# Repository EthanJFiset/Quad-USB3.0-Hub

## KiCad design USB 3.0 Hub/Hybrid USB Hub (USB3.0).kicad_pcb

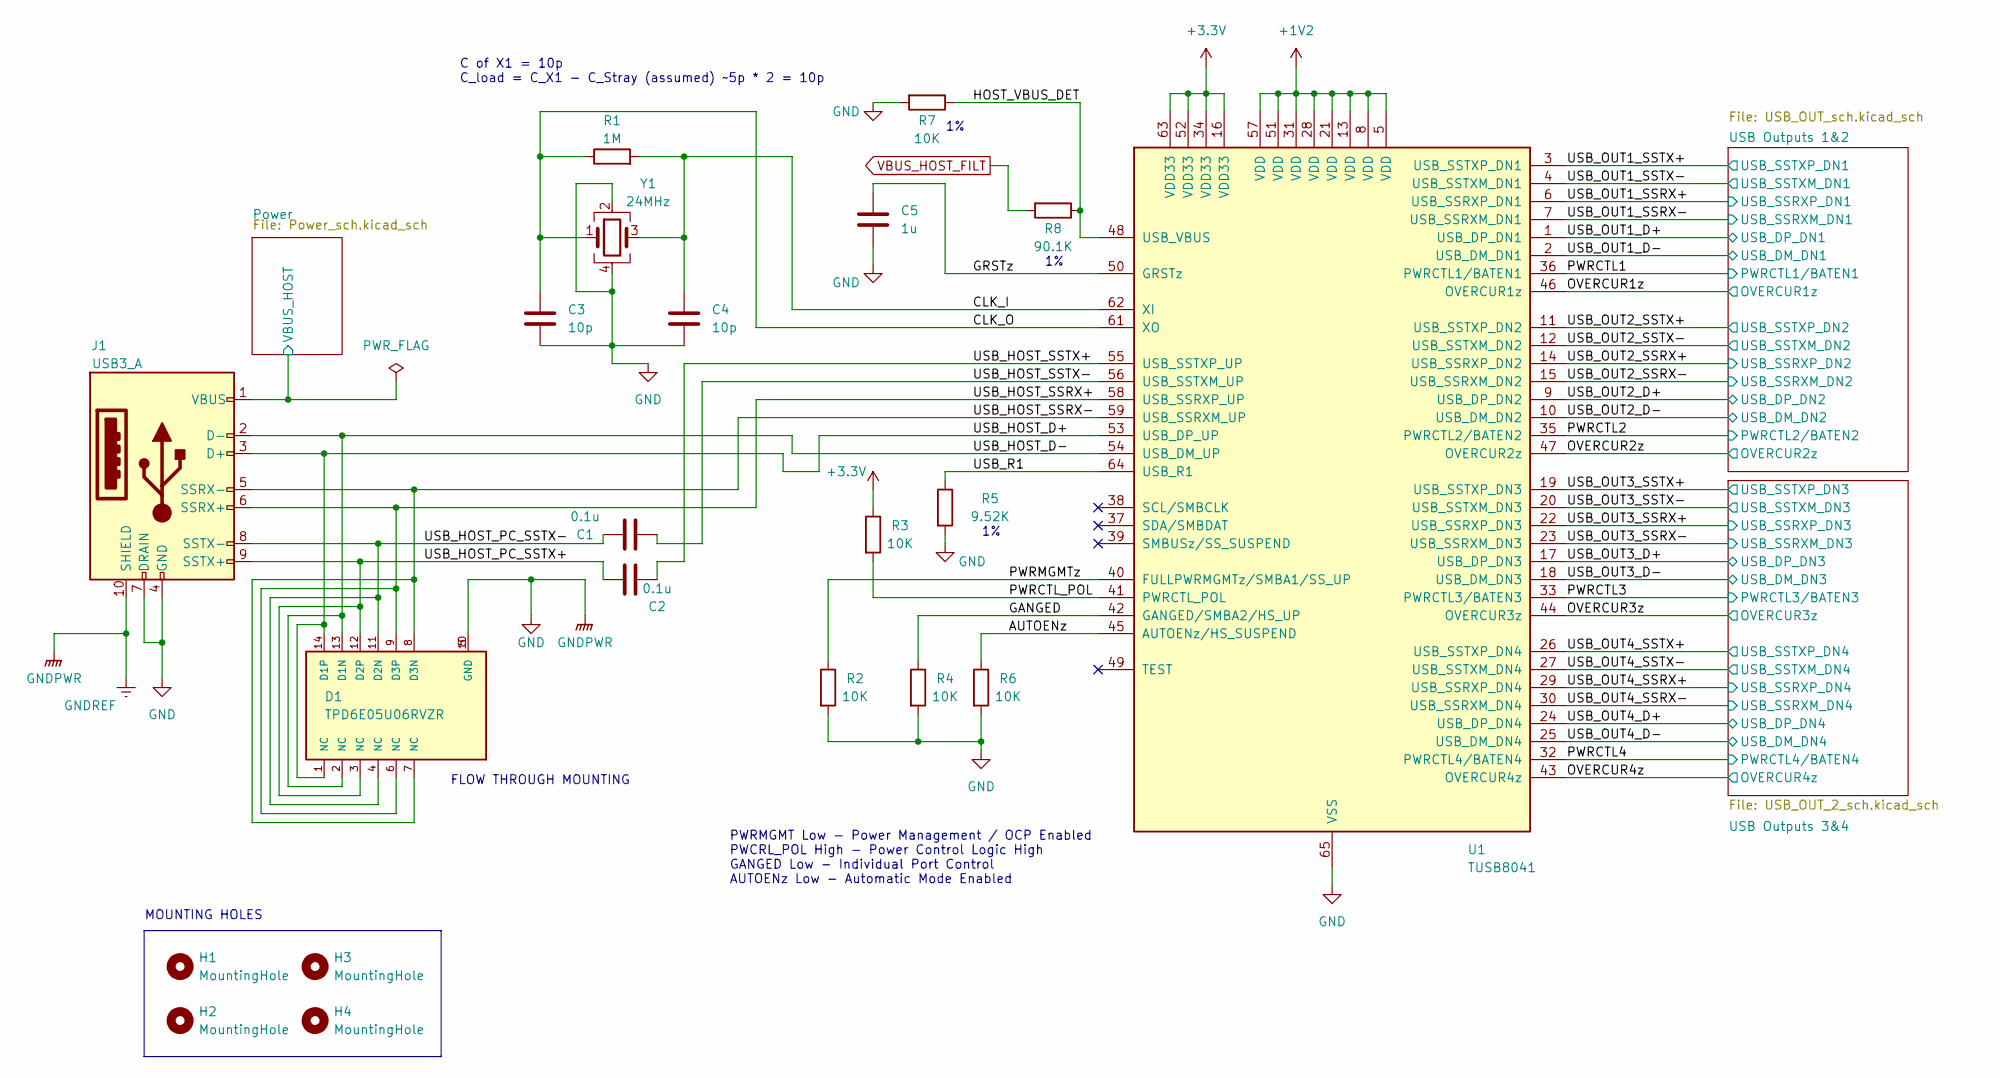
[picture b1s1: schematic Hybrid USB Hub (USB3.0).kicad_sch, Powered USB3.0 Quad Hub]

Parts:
C1, C2: 0.1u; C_0402_1005Metric
C3, C4: 10p; C_0402_1005Metric
C5: 1u; C_0402_1005Metric
D1: TPD6E05U06RVZR; PARTREV L
H1, H2, H3, H4: MountingHole; MountingHole_3.2mm_M3
J1: USB3_A; USB3_A_Molex_48393-001
R1: 1M; R_0402_1005Metric
R2, R3, R4, R6, R7: 10K; R_0402_1005Metric
R5: 9.52K; R_0402_1005Metric
R8: 90.1K; R_0402_1005Metric
U1: TUSB8041; QFN-64-1EP_9x9mm_P0.5mm_EP6x6mm_ThermalVias
Y1: 24MHz; Crystal_SMD_3225-4Pin_3.2x2.5mm

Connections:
+1V2: U1.5 (VDD), U1.8 (VDD), U1.13 (VDD), U1.21 (VDD), U1.28 (VDD), U1.31 (VDD), U1.51 (VDD), U1.57 (VDD); also elsewhere on the board
+3.3V: R3.1, U1.16 (VDD33), U1.34 (VDD33), U1.52 (VDD33), U1.63 (VDD33); also elsewhere on the board
/AUTOENz: R6.1, U1.45 (AUTOENz/HS_SUSPEND)
/CLK_I: C4.1, R1.2, U1.62 (XI), Y1.3
/CLK_O: C3.1, R1.1, U1.61 (XO), Y1.1
/GANGED: R4.1, U1.42 (GANGED/SMBA2/HS_UP)
/GRSTz: C5.1, U1.50 (GRSTz)
/HOST_VBUS_DET: R7.1, R8.1, U1.48 (USB_VBUS)
/OVERCUR1z: U1.46 (OVERCUR1z); also elsewhere on the board
/OVERCUR2z: U1.47 (OVERCUR2z); also elsewhere on the board
/OVERCUR3z: U1.44 (OVERCUR3z); also elsewhere on the board
/OVERCUR4z: U1.43 (OVERCUR4z); also elsewhere on the board
/PWRCTL1: U1.36 (PWRCTL1/BATEN1); also elsewhere on the board
/PWRCTL2: U1.35 (PWRCTL2/BATEN2); also elsewhere on the board
/PWRCTL3: U1.33 (PWRCTL3/BATEN3); also elsewhere on the board
/PWRCTL4: U1.32 (PWRCTL4/BATEN4); also elsewhere on the board
/PWRCTL_POL: R3.2, U1.41 (PWRCTL_POL)
/PWRMGMTz: R2.1, U1.40 (FULLPWRMGMTz/SMBA1/SS_UP)
/Power/VBUS_HOST: J1.1 (VBUS); also elsewhere on the board
/USB_HOST_D+: D1.1 (NC), D1.14 (D1P), J1.3 (D+), U1.53 (USB_DP_UP)
/USB_HOST_D-: D1.2 (NC), D1.13 (D1N), J1.2 (D-), U1.54 (USB_DM_UP)
/USB_HOST_PC_SSTX+: C2.2, D1.3 (NC), D1.12 (D2P), J1.9 (SSTX+)
/USB_HOST_PC_SSTX-: C1.2, D1.4 (NC), D1.11 (D2N), J1.8 (SSTX-)
/USB_HOST_SSRX+: D1.6 (NC), D1.9 (D3P), J1.6 (SSRX+), U1.58 (USB_SSRXP_UP)
/USB_HOST_SSRX-: D1.7 (NC), D1.8 (D3N), J1.5 (SSRX-), U1.59 (USB_SSRXM_UP)
/USB_HOST_SSTX+: C2.1, U1.55 (USB_SSTXP_UP)
/USB_HOST_SSTX-: C1.1, U1.56 (USB_SSTXM_UP)
/USB_OUT1_D+: U1.1 (USB_DP_DN1); also elsewhere on the board
/USB_OUT1_D-: U1.2 (USB_DM_DN1); also elsewhere on the board
/USB_OUT1_SSRX+: U1.6 (USB_SSRXP_DN1); also elsewhere on the board
/USB_OUT1_SSRX-: U1.7 (USB_SSRXM_DN1); also elsewhere on the board
/USB_OUT1_SSTX+: U1.3 (USB_SSTXP_DN1); also elsewhere on the board
/USB_OUT1_SSTX-: U1.4 (USB_SSTXM_DN1); also elsewhere on the board
/USB_OUT2_D+: U1.9 (USB_DP_DN2); also elsewhere on the board
/USB_OUT2_D-: U1.10 (USB_DM_DN2); also elsewhere on the board
/USB_OUT2_SSRX+: U1.14 (USB_SSRXP_DN2); also elsewhere on the board
/USB_OUT2_SSRX-: U1.15 (USB_SSRXM_DN2); also elsewhere on the board
/USB_OUT2_SSTX+: U1.11 (USB_SSTXP_DN2); also elsewhere on the board
/USB_OUT2_SSTX-: U1.12 (USB_SSTXM_DN2); also elsewhere on the board
/USB_OUT3_D+: U1.17 (USB_DP_DN3); also elsewhere on the board
/USB_OUT3_D-: U1.18 (USB_DM_DN3); also elsewhere on the board
/USB_OUT3_SSRX+: U1.22 (USB_SSRXP_DN3); also elsewhere on the board
/USB_OUT3_SSRX-: U1.23 (USB_SSRXM_DN3); also elsewhere on the board
/USB_OUT3_SSTX+: U1.19 (USB_SSTXP_DN3); also elsewhere on the board
/USB_OUT3_SSTX-: U1.20 (USB_SSTXM_DN3); also elsewhere on the board
/USB_OUT4_D+: U1.24 (USB_DP_DN4); also elsewhere on the board
/USB_OUT4_D-: U1.25 (USB_DM_DN4); also elsewhere on the board
/USB_OUT4_SSRX+: U1.29 (USB_SSRXP_DN4); also elsewhere on the board
/USB_OUT4_SSRX-: U1.30 (USB_SSRXM_DN4); also elsewhere on the board
/USB_OUT4_SSTX+: U1.26 (USB_SSTXP_DN4); also elsewhere on the board
/USB_OUT4_SSTX-: U1.27 (USB_SSTXM_DN4); also elsewhere on the board
/USB_R1: R5.1, U1.64 (USB_R1)
GND: C3.2, C4.2, C5.2, D1.5 (GND), D1.10 (GND), J1.4 (GND), J1.7 (DRAIN), J1.10 (SHIELD), R2.2, R4.2, R5.2, R6.2, R7.2, U1.65 (VSS), Y1.2, Y1.4; also elsewhere on the board
VBUS_HOST_FILT: R8.2

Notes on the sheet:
MOUNTING HOLES
FLOW THROUGH MOUNTING
C of X1 = 10p C_load = C_X1 - C_Stray (assumed) ~5p * 2 = 10p
PWRMGMT Low - Power Management / OCP Enabled PWCRL_POL High - Power Control Logic High GANGED Low - Individual Port Control AUTOENz Low - Automatic Mode Enabled

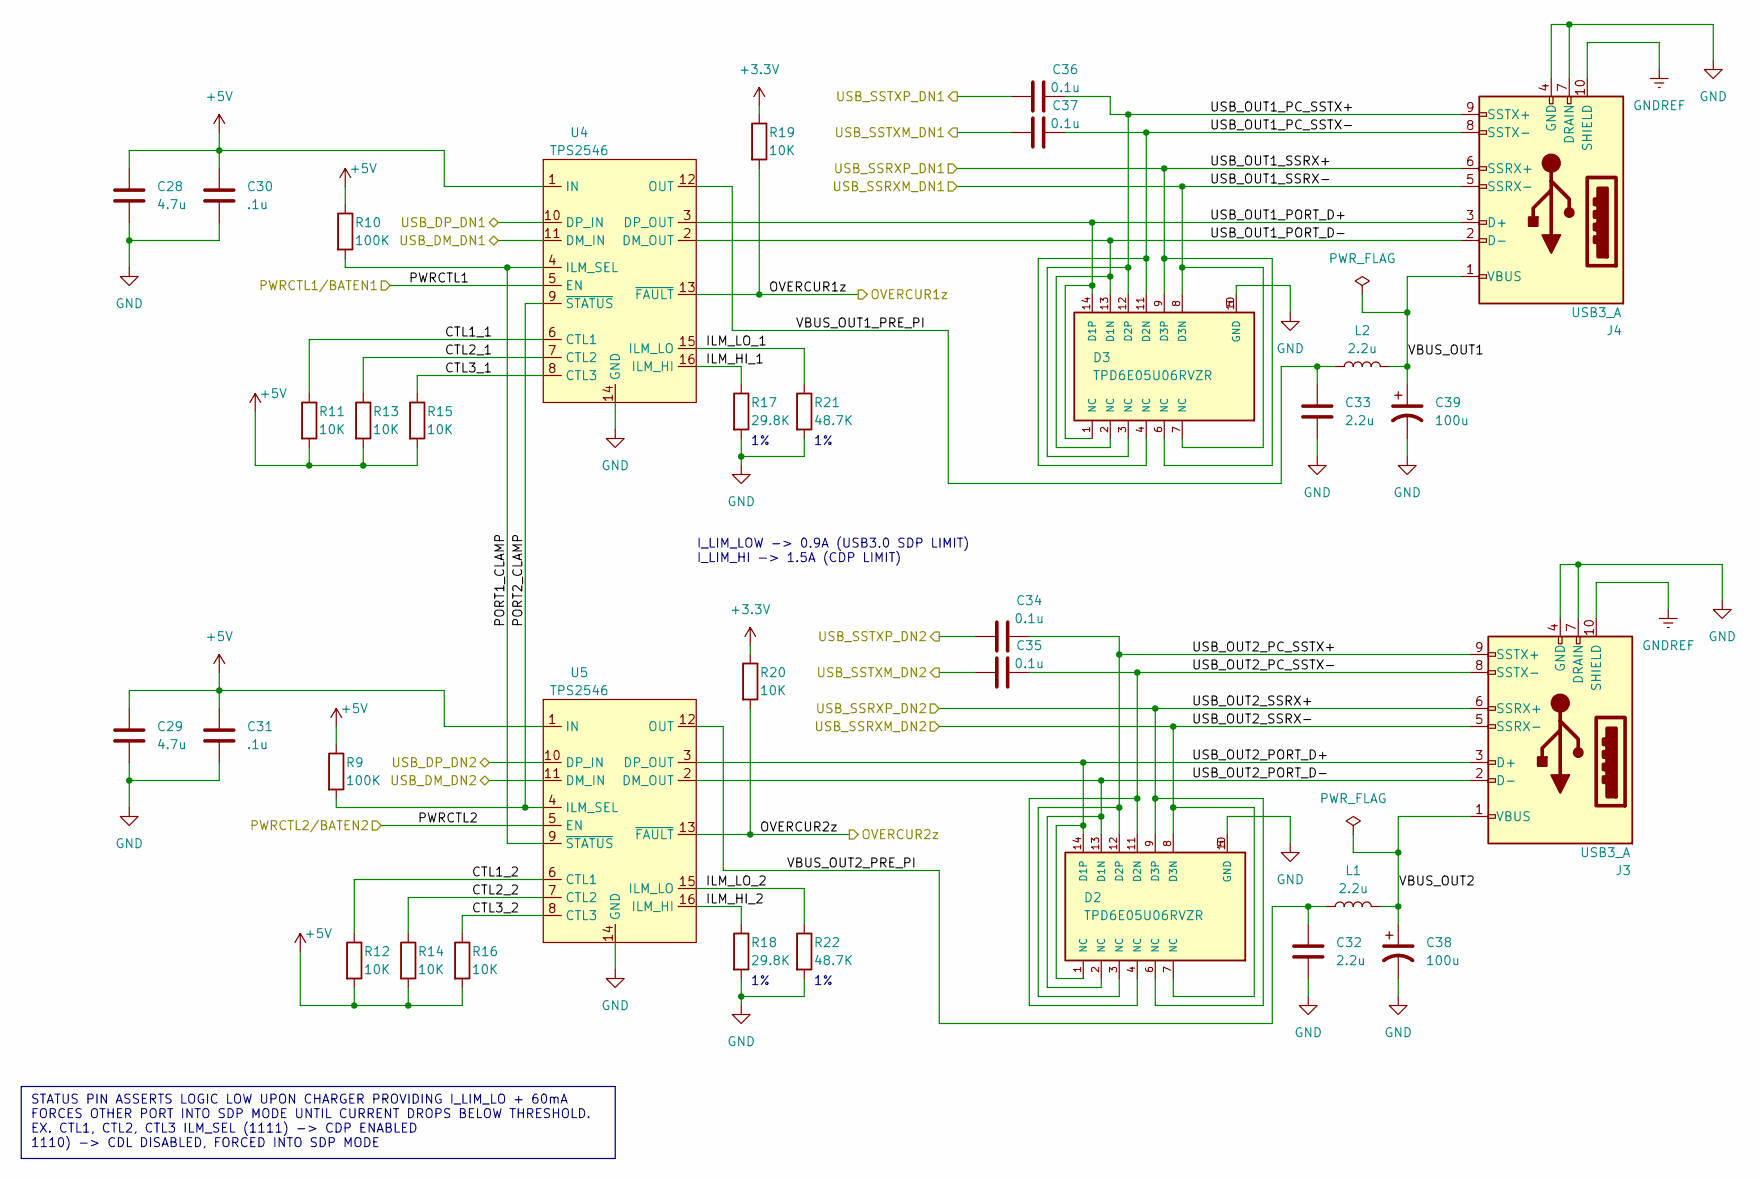
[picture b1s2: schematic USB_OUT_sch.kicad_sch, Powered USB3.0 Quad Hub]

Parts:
C28, C29: 4.7u; C_0402_1005Metric
C30, C31: .1u; C_0402_1005Metric
C32, C33: 2.2u; C_0402_1005Metric
C34, C35, C36, C37: 0.1u; C_0402_1005Metric
C38, C39: 100u; CP_Radial_D5.0mm_P2.50mm
D2, D3: TPD6E05U06RVZR; PARTREV L
J3, J4: USB3_A; USB3_A_Molex_48393-001
L1, L2: 2.2u; L_0402_1005Metric
R9, R10: 100K; R_0402_1005Metric
R11, R12, R13, R14, R15, R16, R19, R20: 10K; R_0402_1005Metric
R17, R18: 29.8K; R_0402_1005Metric
R21, R22: 48.7K; R_0402_1005Metric
U4, U5: TPS2546; TPS2546RTER

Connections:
+3.3V: R19.1, R20.1; also elsewhere on the board
+5V: C28.1, C29.1, C30.1, C31.1, R9.1, R10.1, R11.2, R12.2, R13.2, R14.2, R15.2, R16.2, U4.1 (IN), U5.1 (IN); also elsewhere on the board
/OVERCUR1z: R19.2, U4.13 (~FAULT); also elsewhere on the board
/OVERCUR2z: R20.2, U5.13 (~FAULT); also elsewhere on the board
/PWRCTL1: U4.5 (EN); also elsewhere on the board
/PWRCTL2: U5.5 (EN); also elsewhere on the board
/USB Outputs 1&2/CTL1_1: R11.1, U4.6 (CTL1)
/USB Outputs 1&2/CTL1_2: R12.1, U5.6 (CTL1)
/USB Outputs 1&2/CTL2_1: R13.1, U4.7 (CTL2)
/USB Outputs 1&2/CTL2_2: R14.1, U5.7 (CTL2)
/USB Outputs 1&2/CTL3_1: R15.1, U4.8 (CTL3)
/USB Outputs 1&2/CTL3_2: R16.1, U5.8 (CTL3)
/USB Outputs 1&2/ILM_HI_1: R17.1, U4.16 (ILM_HI)
/USB Outputs 1&2/ILM_HI_2: R18.1, U5.16 (ILM_HI)
/USB Outputs 1&2/ILM_LO_1: R21.1, U4.15 (ILM_LO)
/USB Outputs 1&2/ILM_LO_2: R22.1, U5.15 (ILM_LO)
/USB Outputs 1&2/PORT1_CLAMP: R10.2, U4.4 (ILM_SEL), U5.9 (~STATUS)
/USB Outputs 1&2/PORT2_CLAMP: R9.2, U4.9 (~STATUS), U5.4 (ILM_SEL)
/USB Outputs 1&2/USB_OUT1_PC_SSTX+: C36.2, D3.3 (NC), D3.12 (D2P), J4.9 (SSTX+)
/USB Outputs 1&2/USB_OUT1_PC_SSTX-: C37.2, D3.4 (NC), D3.11 (D2N), J4.8 (SSTX-)
/USB Outputs 1&2/USB_OUT1_PORT_D+: D3.1 (NC), D3.14 (D1P), J4.3 (D+), U4.3 (DP_OUT)
/USB Outputs 1&2/USB_OUT1_PORT_D-: D3.2 (NC), D3.13 (D1N), J4.2 (D-), U4.2 (DM_OUT)
/USB Outputs 1&2/USB_OUT2_PC_SSTX+: C34.2, D2.3 (NC), D2.12 (D2P), J3.9 (SSTX+)
/USB Outputs 1&2/USB_OUT2_PC_SSTX-: C35.2, D2.4 (NC), D2.11 (D2N), J3.8 (SSTX-)
/USB Outputs 1&2/USB_OUT2_PORT_D+: D2.1 (NC), D2.14 (D1P), J3.3 (D+), U5.3 (DP_OUT)
/USB Outputs 1&2/USB_OUT2_PORT_D-: D2.2 (NC), D2.13 (D1N), J3.2 (D-), U5.2 (DM_OUT)
/USB Outputs 1&2/VBUS_OUT1: C39.1, J4.1 (VBUS), L2.2
/USB Outputs 1&2/VBUS_OUT1_PRE_PI: C33.1, L2.1, U4.12 (OUT)
/USB Outputs 1&2/VBUS_OUT2: C38.1, J3.1 (VBUS), L1.2
/USB Outputs 1&2/VBUS_OUT2_PRE_PI: C32.1, L1.1, U5.12 (OUT)
/USB_OUT1_D+: U4.10 (DP_IN); also elsewhere on the board
/USB_OUT1_D-: U4.11 (DM_IN); also elsewhere on the board
/USB_OUT1_SSRX+: D3.6 (NC), D3.9 (D3P), J4.6 (SSRX+); also elsewhere on the board
/USB_OUT1_SSRX-: D3.7 (NC), D3.8 (D3N), J4.5 (SSRX-); also elsewhere on the board
/USB_OUT1_SSTX+: C36.1; also elsewhere on the board
/USB_OUT1_SSTX-: C37.1; also elsewhere on the board
/USB_OUT2_D+: U5.10 (DP_IN); also elsewhere on the board
/USB_OUT2_D-: U5.11 (DM_IN); also elsewhere on the board
/USB_OUT2_SSRX+: D2.6 (NC), D2.9 (D3P), J3.6 (SSRX+); also elsewhere on the board
/USB_OUT2_SSRX-: D2.7 (NC), D2.8 (D3N), J3.5 (SSRX-); also elsewhere on the board
/USB_OUT2_SSTX+: C34.1; also elsewhere on the board
/USB_OUT2_SSTX-: C35.1; also elsewhere on the board
GND: C28.2, C29.2, C30.2, C31.2, C32.2, C33.2, C38.2, C39.2, D2.5 (GND), D2.10 (GND), D3.5 (GND), D3.10 (GND), J3.4 (GND), J3.7 (DRAIN), J3.10 (SHIELD), J4.4 (GND), J4.7 (DRAIN), J4.10 (SHIELD), R17.2, R18.2, R21.2, R22.2, U4.14 (GND), U5.14 (GND); also elsewhere on the board

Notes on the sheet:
STATUS PIN ASSERTS LOGIC LOW UPON CHARGER PROVIDING I_LIM_LO + 60mA FORCES OTHER PORT INTO SDP MODE UNTIL CURRENT DROPS BELOW THRESHOLD. EX. CTL1, CTL2, CTL3 ILM_SEL (1111) -> CDP ENABLED 1110) -> CDL DISABLED, FORCED INTO SDP MODE
I_LIM_LOW -> 0.9A (USB3.0 SDP LIMIT) I_LIM_HI -> 1.5A (CDP LIMIT)

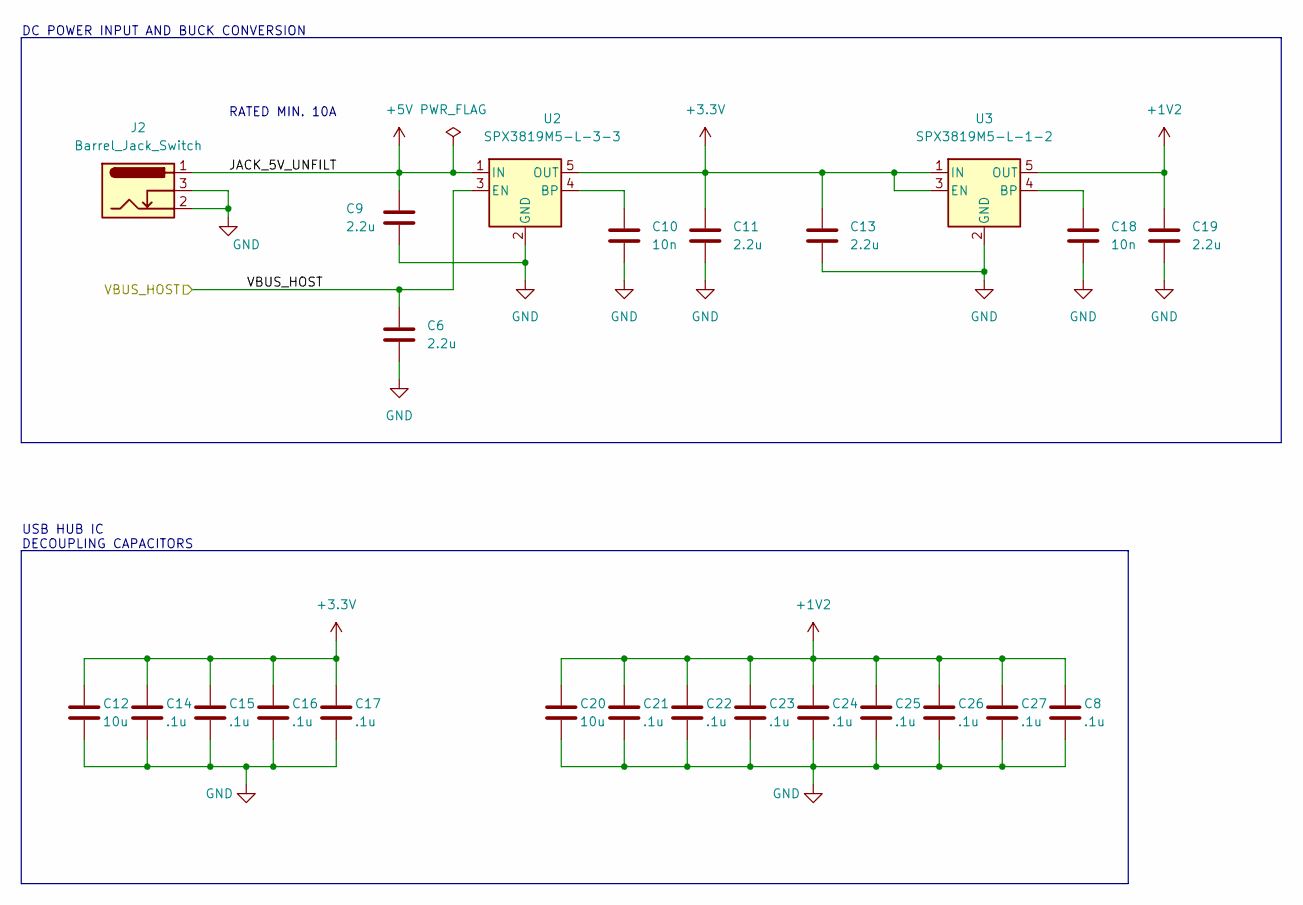
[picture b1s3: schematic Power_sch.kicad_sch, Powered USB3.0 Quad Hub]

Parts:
C6, C9, C11, C13, C19: 2.2u; C_0402_1005Metric
C8, C14, C15, C16, C17, C21, C22, C23, C24, C25, C26, C27: .1u; C_0402_1005Metric
C10, C18: 10n; C_0402_1005Metric
C12, C20: 10u; C_0603_1608Metric
J2: Barrel_Jack_Switch; BarrelJack_CUI_PJ-063AH_Horizontal
U2: SPX3819M5-L-3-3; SOT-23-5
U3: SPX3819M5-L-1-2; SOT-23-5

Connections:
+1V2: C8.1, C19.1, C20.1, C21.1, C22.1, C23.1, C24.1, C25.1, C26.1, C27.1, U3.5 (OUT); also elsewhere on the board
+3.3V: C11.1, C12.1, C13.1, C14.1, C15.1, C16.1, C17.1, U2.5 (OUT), U3.1 (IN), U3.3 (EN); also elsewhere on the board
+5V: C9.1, J2.1, U2.1 (IN); also elsewhere on the board
/Power/VBUS_HOST: C6.1, U2.3 (EN); also elsewhere on the board
GND: C6.2, C8.2, C9.2, C10.2, C11.2, C12.2, C13.2, C14.2, C15.2, C16.2, C17.2, C18.2, C19.2, C20.2, C21.2, C22.2, C23.2, C24.2, C25.2, C26.2, C27.2, J2.2, J2.3, U2.2 (GND), U3.2 (GND); also elsewhere on the board
unnamed: C10.1, U2.4 (BP)
unnamed: C18.1, U3.4 (BP)

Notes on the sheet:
DC POWER INPUT AND BUCK CONVERSION
USB HUB IC DECOUPLING CAPACITORS
RATED MIN. 10A

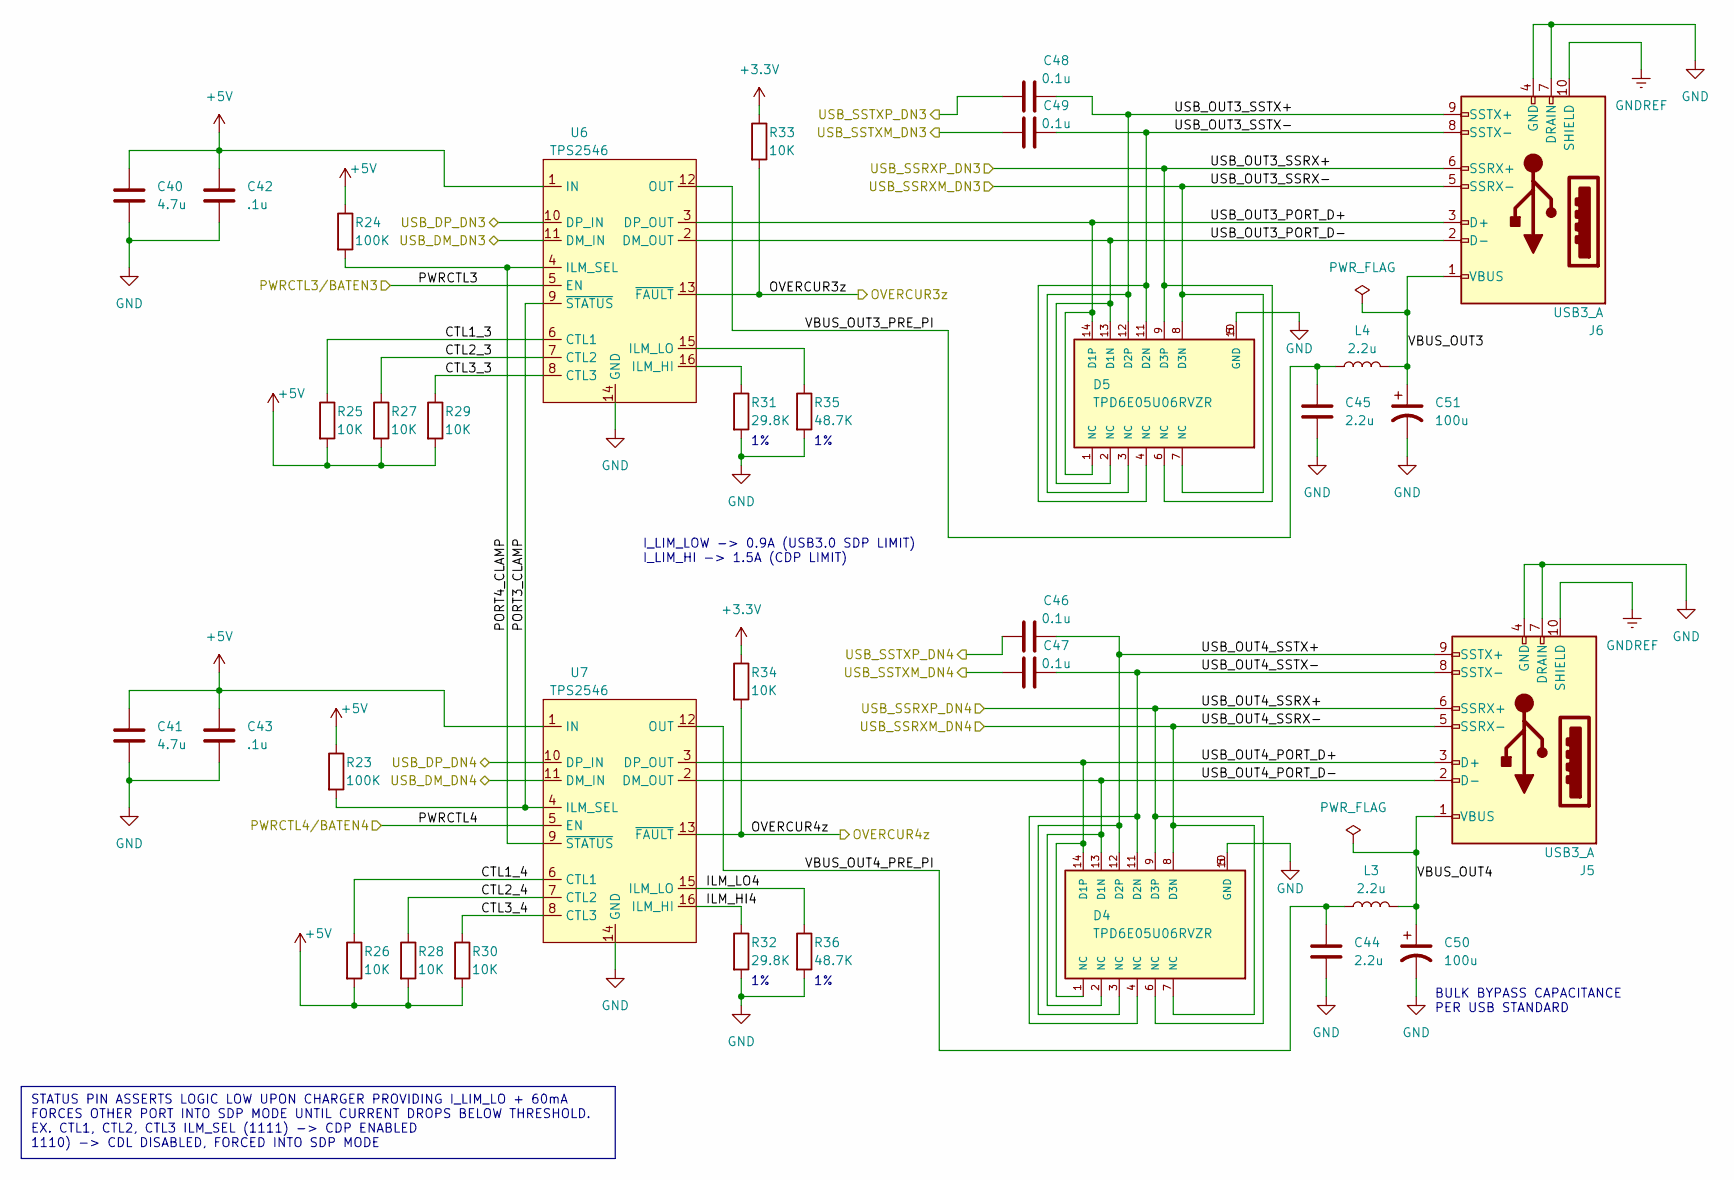
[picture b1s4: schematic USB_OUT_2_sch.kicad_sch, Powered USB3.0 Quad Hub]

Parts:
C40, C41: 4.7u; C_0402_1005Metric
C42, C43: .1u; C_0402_1005Metric
C44, C45: 2.2u; C_0402_1005Metric
C46, C47, C48, C49: 0.1u; C_0402_1005Metric
C50, C51: 100u; CP_Radial_D5.0mm_P2.50mm
D4, D5: TPD6E05U06RVZR; PARTREV L
J5, J6: USB3_A; USB3_A_Molex_48393-001
L3, L4: 2.2u; L_0402_1005Metric
R23, R24: 100K; R_0402_1005Metric
R25, R26, R27, R28, R29, R30, R33, R34: 10K; R_0402_1005Metric
R31, R32: 29.8K; R_0402_1005Metric
R35, R36: 48.7K; R_0402_1005Metric
U6, U7: TPS2546; TPS2546RTER

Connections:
+3.3V: R33.1, R34.1; also elsewhere on the board
+5V: C40.1, C41.1, C42.1, C43.1, R23.1, R24.1, R25.2, R26.2, R27.2, R28.2, R29.2, R30.2, U6.1 (IN), U7.1 (IN); also elsewhere on the board
/OVERCUR3z: R33.2, U6.13 (~FAULT); also elsewhere on the board
/OVERCUR4z: R34.2, U7.13 (~FAULT); also elsewhere on the board
/PWRCTL3: U6.5 (EN); also elsewhere on the board
/PWRCTL4: U7.5 (EN); also elsewhere on the board
/USB Outputs 3&4/CTL1_3: R25.1, U6.6 (CTL1)
/USB Outputs 3&4/CTL1_4: R26.1, U7.6 (CTL1)
/USB Outputs 3&4/CTL2_3: R27.1, U6.7 (CTL2)
/USB Outputs 3&4/CTL2_4: R28.1, U7.7 (CTL2)
/USB Outputs 3&4/CTL3_3: R29.1, U6.8 (CTL3)
/USB Outputs 3&4/CTL3_4: R30.1, U7.8 (CTL3)
/USB Outputs 3&4/ILM_HI4: R32.1, U7.16 (ILM_HI)
/USB Outputs 3&4/ILM_LO4: R36.1, U7.15 (ILM_LO)
/USB Outputs 3&4/PORT3_CLAMP: R23.2, U6.9 (~STATUS), U7.4 (ILM_SEL)
/USB Outputs 3&4/PORT4_CLAMP: R24.2, U6.4 (ILM_SEL), U7.9 (~STATUS)
/USB Outputs 3&4/USB_OUT3_PORT_D+: D5.1 (NC), D5.14 (D1P), J6.3 (D+), U6.3 (DP_OUT)
/USB Outputs 3&4/USB_OUT3_PORT_D-: D5.2 (NC), D5.13 (D1N), J6.2 (D-), U6.2 (DM_OUT)
/USB Outputs 3&4/USB_OUT3_SSTX+: C48.2, D5.3 (NC), D5.12 (D2P), J6.9 (SSTX+)
/USB Outputs 3&4/USB_OUT3_SSTX-: C49.2, D5.4 (NC), D5.11 (D2N), J6.8 (SSTX-)
/USB Outputs 3&4/USB_OUT4_PORT_D+: D4.1 (NC), D4.14 (D1P), J5.3 (D+), U7.3 (DP_OUT)
/USB Outputs 3&4/USB_OUT4_PORT_D-: D4.2 (NC), D4.13 (D1N), J5.2 (D-), U7.2 (DM_OUT)
/USB Outputs 3&4/USB_OUT4_SSTX+: C46.2, D4.3 (NC), D4.12 (D2P), J5.9 (SSTX+)
/USB Outputs 3&4/USB_OUT4_SSTX-: C47.2, D4.4 (NC), D4.11 (D2N), J5.8 (SSTX-)
/USB Outputs 3&4/VBUS_OUT3: C51.1, J6.1 (VBUS), L4.2
/USB Outputs 3&4/VBUS_OUT3_PRE_PI: C45.1, L4.1, U6.12 (OUT)
/USB Outputs 3&4/VBUS_OUT4: C50.1, J5.1 (VBUS), L3.2
/USB Outputs 3&4/VBUS_OUT4_PRE_PI: C44.1, L3.1, U7.12 (OUT)
/USB_OUT3_D+: U6.10 (DP_IN); also elsewhere on the board
/USB_OUT3_D-: U6.11 (DM_IN); also elsewhere on the board
/USB_OUT3_SSRX+: D5.6 (NC), D5.9 (D3P), J6.6 (SSRX+); also elsewhere on the board
/USB_OUT3_SSRX-: D5.7 (NC), D5.8 (D3N), J6.5 (SSRX-); also elsewhere on the board
/USB_OUT3_SSTX+: C48.1; also elsewhere on the board
/USB_OUT3_SSTX-: C49.1; also elsewhere on the board
/USB_OUT4_D+: U7.10 (DP_IN); also elsewhere on the board
/USB_OUT4_D-: U7.11 (DM_IN); also elsewhere on the board
/USB_OUT4_SSRX+: D4.6 (NC), D4.9 (D3P), J5.6 (SSRX+); also elsewhere on the board
/USB_OUT4_SSRX-: D4.7 (NC), D4.8 (D3N), J5.5 (SSRX-); also elsewhere on the board
/USB_OUT4_SSTX+: C46.1; also elsewhere on the board
/USB_OUT4_SSTX-: C47.1; also elsewhere on the board
GND: C40.2, C41.2, C42.2, C43.2, C44.2, C45.2, C50.2, C51.2, D4.5 (GND), D4.10 (GND), D5.5 (GND), D5.10 (GND), J5.4 (GND), J5.7 (DRAIN), J5.10 (SHIELD), J6.4 (GND), J6.7 (DRAIN), J6.10 (SHIELD), R31.2, R32.2, R35.2, R36.2, U6.14 (GND), U7.14 (GND); also elsewhere on the board
unnamed: R31.1, U6.16 (ILM_HI)
unnamed: R35.1, U6.15 (ILM_LO)

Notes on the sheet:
STATUS PIN ASSERTS LOGIC LOW UPON CHARGER PROVIDING I_LIM_LO + 60mA FORCES OTHER PORT INTO SDP MODE UNTIL CURRENT DROPS BELOW THRESHOLD. EX. CTL1, CTL2, CTL3 ILM_SEL (1111) -> CDP ENABLED 1110) -> CDL DISABLED, FORCED INTO SDP MODE
I_LIM_LOW -> 0.9A (USB3.0 SDP LIMIT) I_LIM_HI -> 1.5A (CDP LIMIT)
BULK BYPASS CAPACITANCE PER USB STANDARD

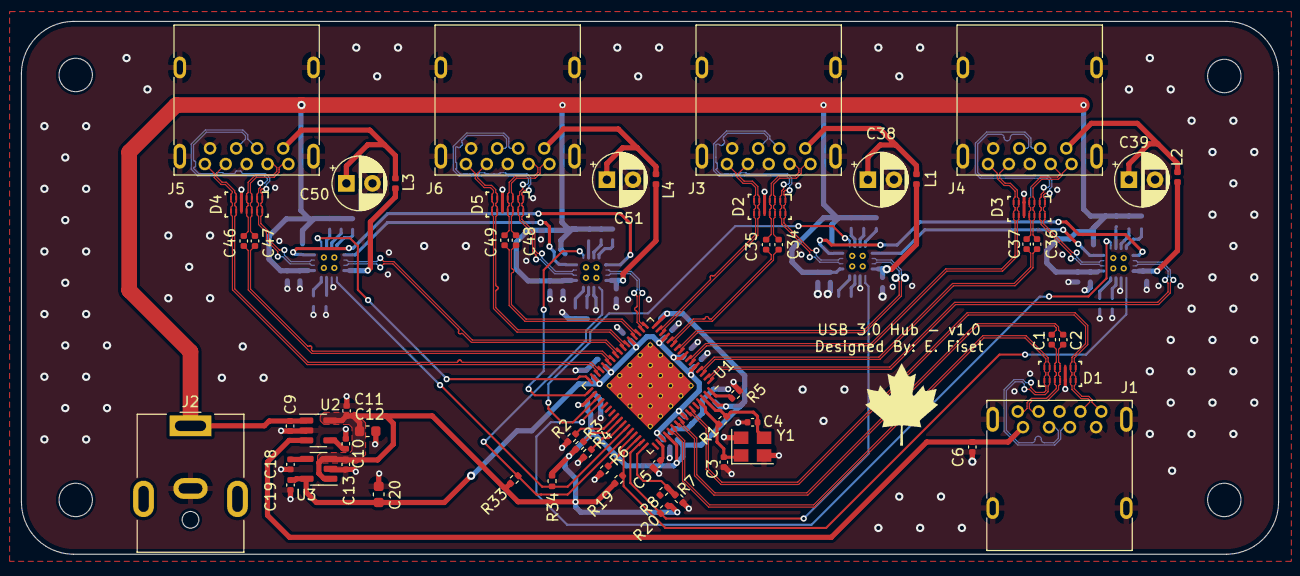
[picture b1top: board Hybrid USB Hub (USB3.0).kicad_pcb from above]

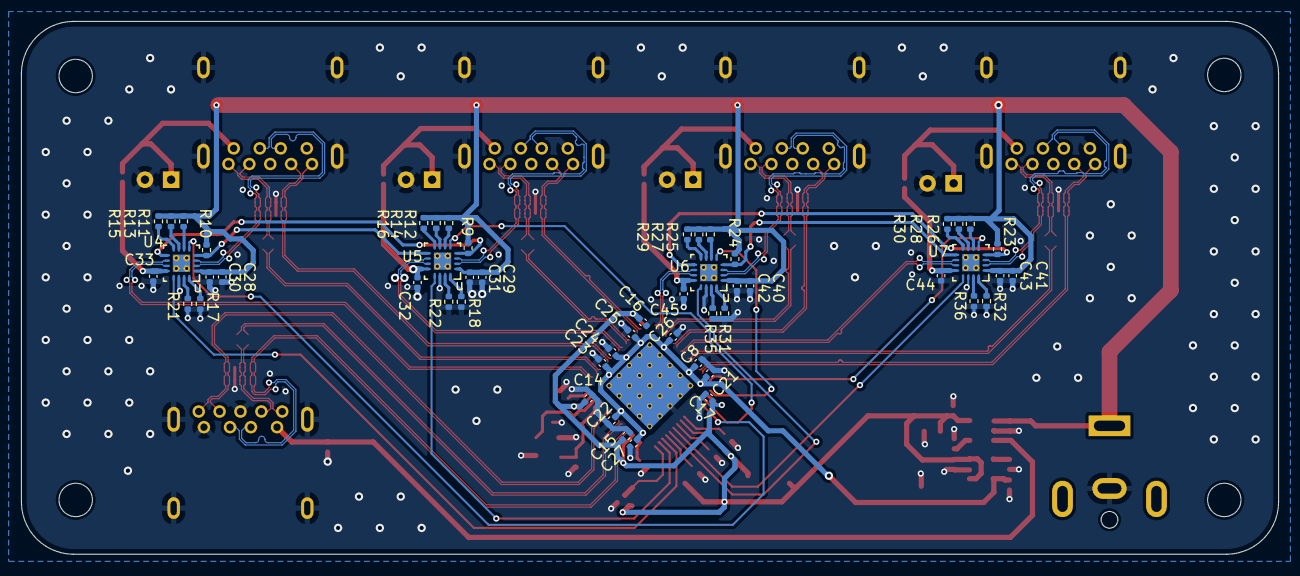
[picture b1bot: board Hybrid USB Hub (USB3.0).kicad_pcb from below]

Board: 4 copper layers, 120.4 x 51.0 mm, 113 parts (52 on the bottom side), 104 nets.
